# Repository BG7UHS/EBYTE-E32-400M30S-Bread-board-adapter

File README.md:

# EBYTE-E32-400M30S-Bread-board-adapter
EBYTE E32-400M30S KICAD file

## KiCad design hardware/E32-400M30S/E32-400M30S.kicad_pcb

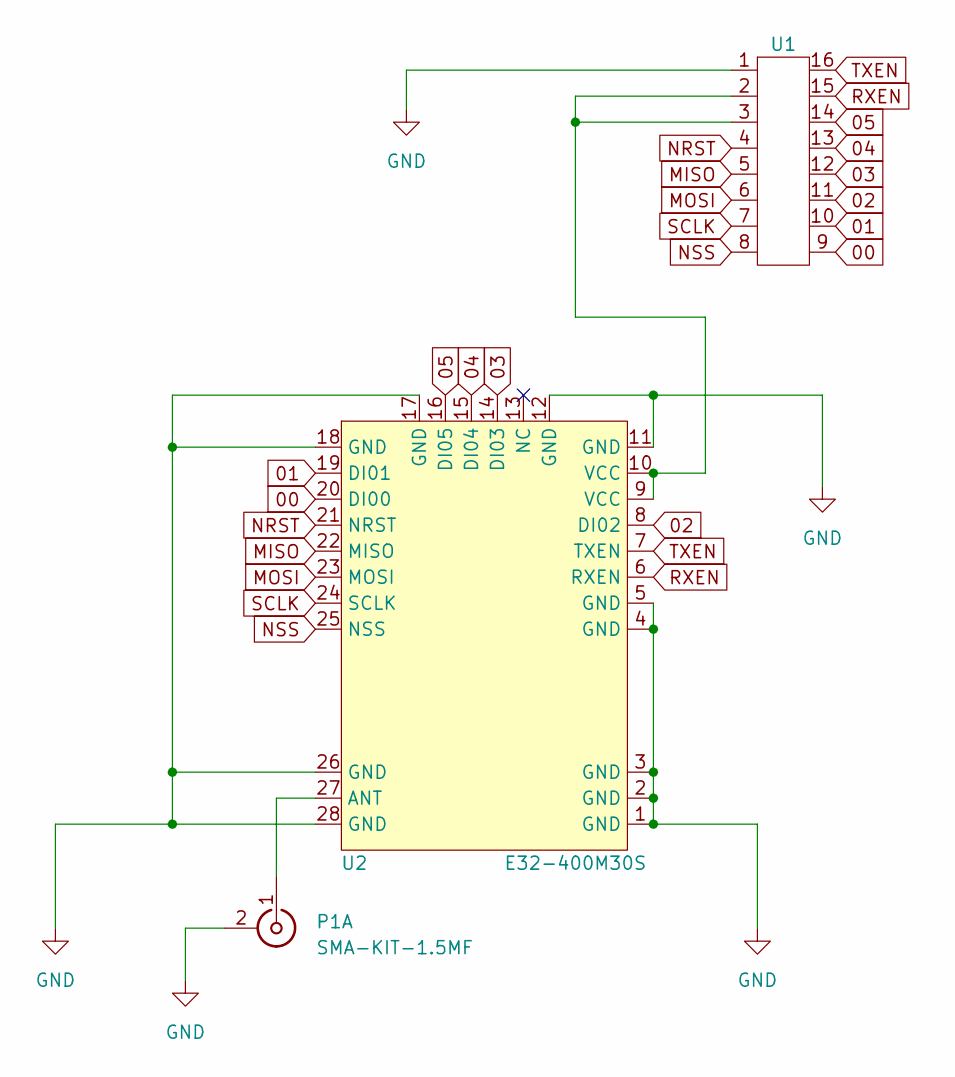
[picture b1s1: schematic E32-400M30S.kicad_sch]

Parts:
P1: SMA-KIT-1.5MF; SMA-EDGE
U1: 82
U2: E32-400M30S

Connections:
00: U1.9, U2.20 (DI00)
01: U1.10, U2.19 (DI01)
02: U1.11, U2.8 (DI02)
03: U1.12, U2.14 (DI03)
04: U1.13, U2.15 (DI04)
05: U1.14, U2.16 (DI05)
GND: P1.2 (SHIELD), U1.1, U2.1 (GND), U2.2 (GND), U2.3 (GND), U2.4 (GND), U2.5 (GND), U2.11 (GND), U2.12 (GND), U2.17 (GND), U2.18 (GND), U2.26 (GND), U2.28 (GND)
MISO: U1.5, U2.22 (MISO)
MOSI: U1.6, U2.23 (MOSI)
NRST: U1.4, U2.21 (NRST)
NSS: U1.8, U2.25 (NSS)
unnamed: P1.1 (RF), U2.27 (ANT)
unnamed: U1.2, U1.3, U2.9 (VCC), U2.10 (VCC)
RXEN: U1.15, U2.6 (RXEN)
SCLK: U1.7, U2.24 (SCLK)
TXEN: U1.16, U2.7 (TXEN)

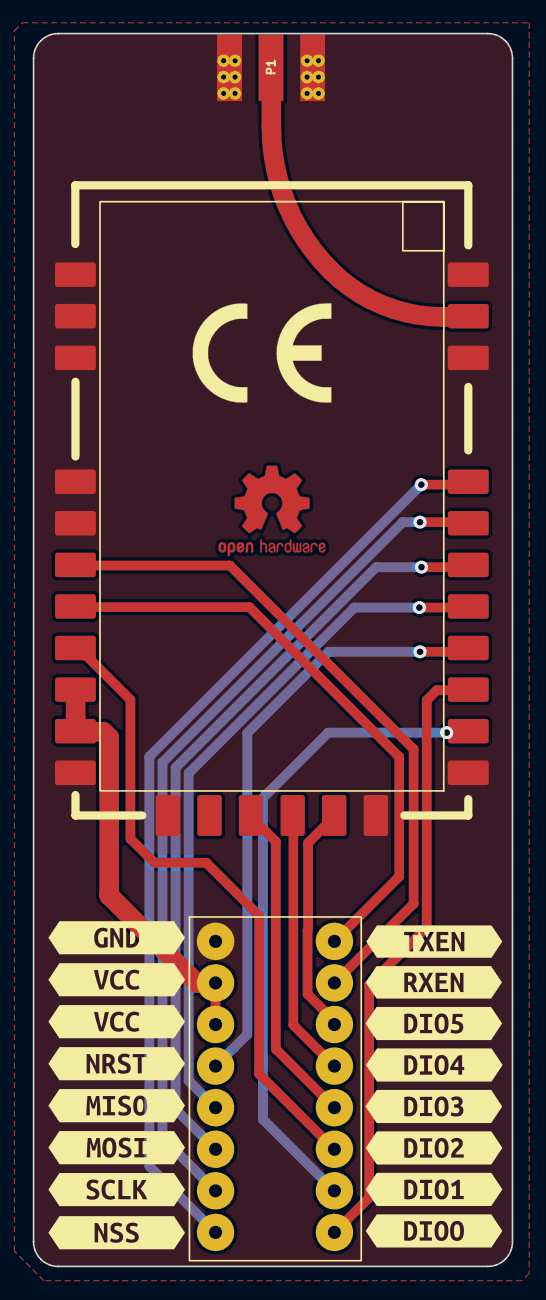
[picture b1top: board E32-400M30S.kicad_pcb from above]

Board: 2 copper layers, 29.3 x 75.3 mm, 19 parts (0 on the bottom side), 16 nets.

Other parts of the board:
kibuzzard-645AF6A3: G***; kibuzzard-645AF6A3
kibuzzard-645AF6AB: G***; kibuzzard-645AF6AB
kibuzzard-645AF6BF: G***; kibuzzard-645AF6BF
kibuzzard-645AF6CA: G***; kibuzzard-645AF6CA
kibuzzard-645AF6D8: G***; kibuzzard-645AF6D8
kibuzzard-645AF6DE: G***; kibuzzard-645AF6DE
kibuzzard-645AF6E5: G***; kibuzzard-645AF6E5
kibuzzard-645AF72C: G***; kibuzzard-645AF72C
kibuzzard-645AF73E: G***; kibuzzard-645AF73E
kibuzzard-645AF74B: G***; kibuzzard-645AF74B
kibuzzard-645AF732: G***; kibuzzard-645AF732
kibuzzard-645AF738: G***; kibuzzard-645AF738
kibuzzard-645AF745: G***; kibuzzard-645AF745
kibuzzard-645AF751: G***; kibuzzard-645AF751
kibuzzard-645AF835: G***; kibuzzard-645AF835
kibuzzard-645AF847: G***; kibuzzard-645AF847

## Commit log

2023-05-09 Create hardware
